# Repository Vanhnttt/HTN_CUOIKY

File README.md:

# DỰ ÁN MÁY HIỆN SÓNG MINI (STM32F103C8T6 + TFT ST7735 1.8")
---
## 📂 CẤU TRÚC DỰ ÁN ĐÃ TÁCH MODULE HOÀN CHỈNH
```text
oscilloscope/
├── .vscode/
│   └── c_cpp_properties.json   (Cấu hình Include & IntelliSense cho VS Code)
├── Core/
│   ├── Inc/
│   │   │   /* --- 1. KHỐI TÍNH TOÁN & XỬ LÝ TÍN HIỆU (THEO ĐỀ BÀI) --- */
│   │   ├── signal_calc.h       (Tìm trigger, tính Vmin/Vmax/Vpp, tần số cắt ngưỡng)
│   │   │
│   │   │   /* --- 2. CÁC MODULE ỨNG DỤNG MÁY HIỆN SÓNG --- */
│   │   ├── scope_acquisition.h (Thu thập ADC1 kích TIM3 TRGO + DMA Double buffer)
│   │   ├── test_signal.h       (Phát xung vuông PWM 1 kHz test sóng tại PA8)
│   │   ├── st7735.h            (Driver màn hình màu TFT ST7735 qua SPI1)
│   │   ├── scope_gui.h         (Hiển thị lưới chia ô, dạng sóng, OSD thông số)
│   │   ├── scope_input.h       (Đọc Rotary Encoder TIM4 & nút bấm PB8, PB9)
│   │   ├── scope_fft.h         (Chế độ FFT hiển thị phổ tần số Radix-2)
│   │   │
│   │   │   /* --- 3. CÁC MODULE NGOẠI VI PHẦN CỨNG (TÁCH KHỎI MAIN) --- */
│   │   ├── sys_clock.h         (Cấu hình xung nhịp 72 MHz: HSE + PLL)
│   │   ├── gpio.h              (Cấu hình chân I/O màn hình, nút bấm, ADC)
│   │   ├── dma.h               (Cấu hình DMA1 Channel 1 cho ADC1)
│   │   ├── adc.h               (Cấu hình ADC1 kích hoạt bởi TIM3 TRGO)
│   │   ├── spi.h               (Cấu hình SPI1 Master 9 MHz)
│   │   ├── tim.h               (Cấu hình TIM1 PWM, TIM3 ADC TRGO, TIM4 Encoder)
│   │   ├── stm32f1xx_it.h      (Khai báo các ngắt hệ thống & ngoại vi)
│   │   └── main.h              (Khai báo thư viện HAL & Error_Handler)
│   │
│   └── Src/
│       ├── main.c              (Hàm main điều phối luồng chạy - RẤT NGẮN GỌN)
│       ├── signal_calc.c       (Thuật toán tính toán Vpp, Freq, Trigger)
│       ├── scope_acquisition.c
│       ├── test_signal.c
│       ├── st7735.c
│       ├── scope_gui.c
│       ├── scope_input.c
│       ├── scope_fft.c
│       ├── sys_clock.c
│       ├── gpio.c
│       ├── dma.c
│       ├── adc.c
│       ├── spi.c
│       ├── tim.c
│       ├── stm32f1xx_it.c      (Hàm phục vụ ngắt DMA, ngắt hệ thống)
│       └── stm32f1xx_hal_msp.c (Hàm MSP cấu hình chân & xung ngoại vi)
└── README.md
```

---

## 📌 CHI TIẾT CÁC HÀM TRONG KHỐI TÍNH TOÁN (`signal_calc.c`)

Khối này giải quyết trọn vẹn yêu cầu trong ảnh:
> *"Xử lý: tìm điểm trigger, tính Vmin/Vmax/Vpp, tần số (đếm cắt ngưỡng)"*

1. **`SigCalc_Tinh_Vmin_Vmax_Vpp(snap_buf)`**:
   - Quét 256 mẫu ADC để tìm mẫu cực tiểu và cực đại.
   - Tính toán điện áp chuẩn: $V_{\min}$, $V_{\max}$ và điện áp đỉnh - đỉnh $V_{\text{pp}} = V_{\max} - V_{\min}$.
2. **`SigCalc_TinhTanSo_DemCatNguong(snap_buf, snap_tb)`**:
   - Xác định ngưỡng trung bình `mid = (max + min)/2` và dải trễ `hyst`.
   - Đếm số lần tín hiệu cắt qua ngưỡng cạnh lên để tính chính xác chu kỳ và tần số tín hiệu $f = \frac{f_s \times (edges - 1)}{\Delta samples}$.
3. **`SigCalc_TimDiemTrigger(snap_buf, trig_lvl)`**:
   - Dò tìm điểm tín hiệu vượt ngưỡng `trig_lvl` theo cạnh lên có dải trễ chống nhiễu (hysteresis) để khóa dạng sóng đứng yên trên màn hình.
4. **`SigCalc_ChuanBiDangSong(...)`**:
   - Ánh xạ các điểm mẫu quanh điểm trigger sang tọa độ cột $X$ và hàng $Y$ trên màn hình ST7735.

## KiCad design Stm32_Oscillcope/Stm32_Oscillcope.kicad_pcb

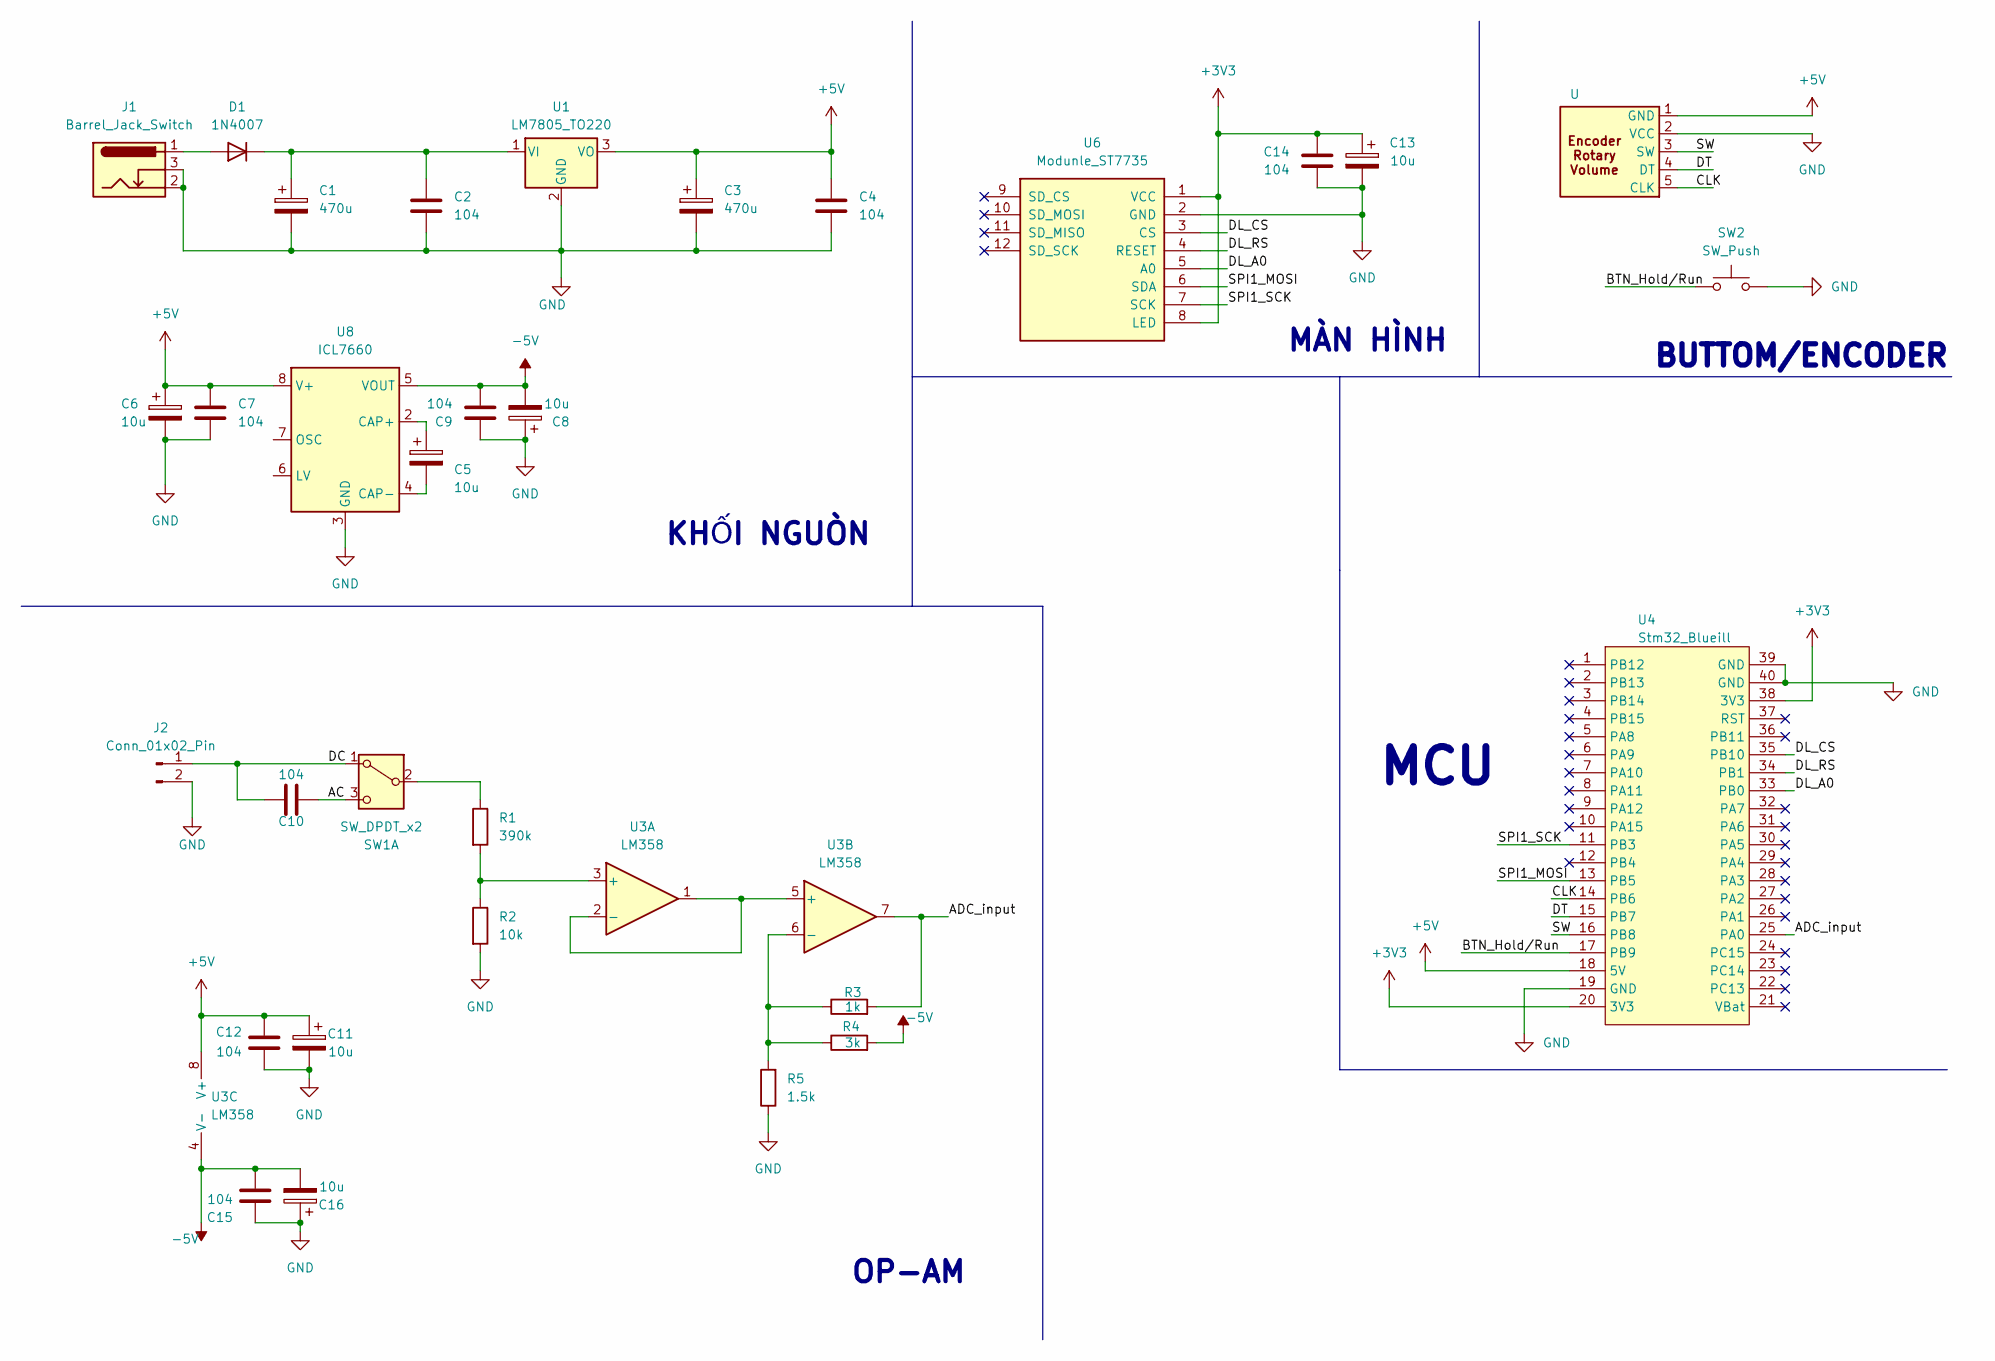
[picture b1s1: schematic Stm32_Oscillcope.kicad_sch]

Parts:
C1, C3: 470u; CP_Radial_D10.0mm_P5.00mm
C2, C4, C7, C9, C10, C12, C14, C15: 104; C_Disc_D3.0mm_W1.6mm_P2.50mm
C5, C6, C11, C13, C16: 10u; CP_Radial_D5.0mm_P2.00mm
C8: 10u; CP_Radial_D5.0mm_P2.50mm
D1: 1N4007; D_DO-41_SOD81_P10.16mm_Horizontal
J1: Barrel_Jack_Switch; BarrelJack_GCT_DCJ200-10-A_Horizontal
J2: Conn_01x02_Pin; TerminalBlock_Phoenix_MKDS-1,5-2_1x02_P5.00mm_Horizontal
R1: 390k; R_Axial_DIN0411_L9.9mm_D3.6mm_P12.70mm_Horizontal
R2: 10k; R_Axial_DIN0411_L9.9mm_D3.6mm_P12.70mm_Horizontal
R3: 1k; R_Axial_DIN0411_L9.9mm_D3.6mm_P12.70mm_Horizontal
R4: 3k; R_Axial_DIN0411_L9.9mm_D3.6mm_P12.70mm_Horizontal
R5: 1.5k; R_Axial_DIN0411_L9.9mm_D3.6mm_P12.70mm_Horizontal
SW1: SW_DPDT_x2; SW_Slide_SPDT_Straight_CK_OS102011MS2Q
SW2: SW_Push; SW_PUSH_6mm
U1: LM7805_TO220; TO-220-3_Vertical
U2: U; Module_Encoder
U3: LM358; DIP-8_W7.62mm_Socket
U4: Stm32_Blueill; YAAJ_BluePill_1
U6: Modunle_ST7735; Display_ST7735
U8: ICL7660; DIP-8_W7.62mm_Socket

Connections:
+3V3: C13.1, C14.1, U4.20 (3V3), U4.38 (3V3), U6.1 (VCC), U6.8 (LED)
+5V: C3.1, C4.1, C6.1, C7.1, C11.1, C12.1, U1.3 (VO), U2.1 (GND), U3.8 (V+), U4.18 (5V), U8.8 (V+)
-5V: C8.2, C9.2, C15.2, C16.2, R4.2, U3.4 (V-), U8.5 (VOUT)
/AC: C10.2, SW1.3 (C)
/ADC_input: R3.2, U3.7, U4.25 (PA0)
/BTN_Hold/Run: SW2.1, U4.17 (PB9)
/CLK: U2.5 (CLK), U4.14 (PB6)
/DC: C10.1, J2.1, SW1.1 (A)
/DL_A0: U4.33 (PB0), U6.5 (A0)
/DL_CS: U4.35 (PB10), U6.3 (CS)
/DL_RS: U4.34 (PB1), U6.4 (RESET)
/DT: U2.4 (DT), U4.15 (PB7)
/SPI1_MOSI: U4.13 (PB5), U6.6 (SDA)
/SPI1_SCK: U4.11 (PB3), U6.7 (SCK)
/SW: U2.3 (SW), U4.16 (PB8)
GND: C1.2, C2.2, C3.2, C4.2, C6.2, C7.2, C8.1, C9.1, C11.2, C12.2, C13.2, C14.2, C15.1, C16.1, J1.2, J1.3, J2.2, R2.2, R5.1, SW2.2, U1.2 (GND), U2.2 (VCC), U4.19 (GND), U4.39 (GND), U4.40 (GND), U6.2 (GND), U8.3 (GND)
unnamed: D1.2 (A), J1.1
unnamed: C1.1, C2.1, D1.1 (K), U1.1 (VI)
unnamed: R1.1, SW1.2 (B)
unnamed: R1.2, R2.1, U3.3 (+)
unnamed: U3.1, U3.2 (-), U3.5 (+)
unnamed: R3.1, R4.1, R5.2, U3.6 (-)
unnamed: C5.1, U8.2 (CAP+)
unnamed: C5.2, U8.4 (CAP-)

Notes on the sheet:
MCU
MÀN HÌNH
KHỐI NGUÒN
BUTTOM/ENCODER
OP-AM

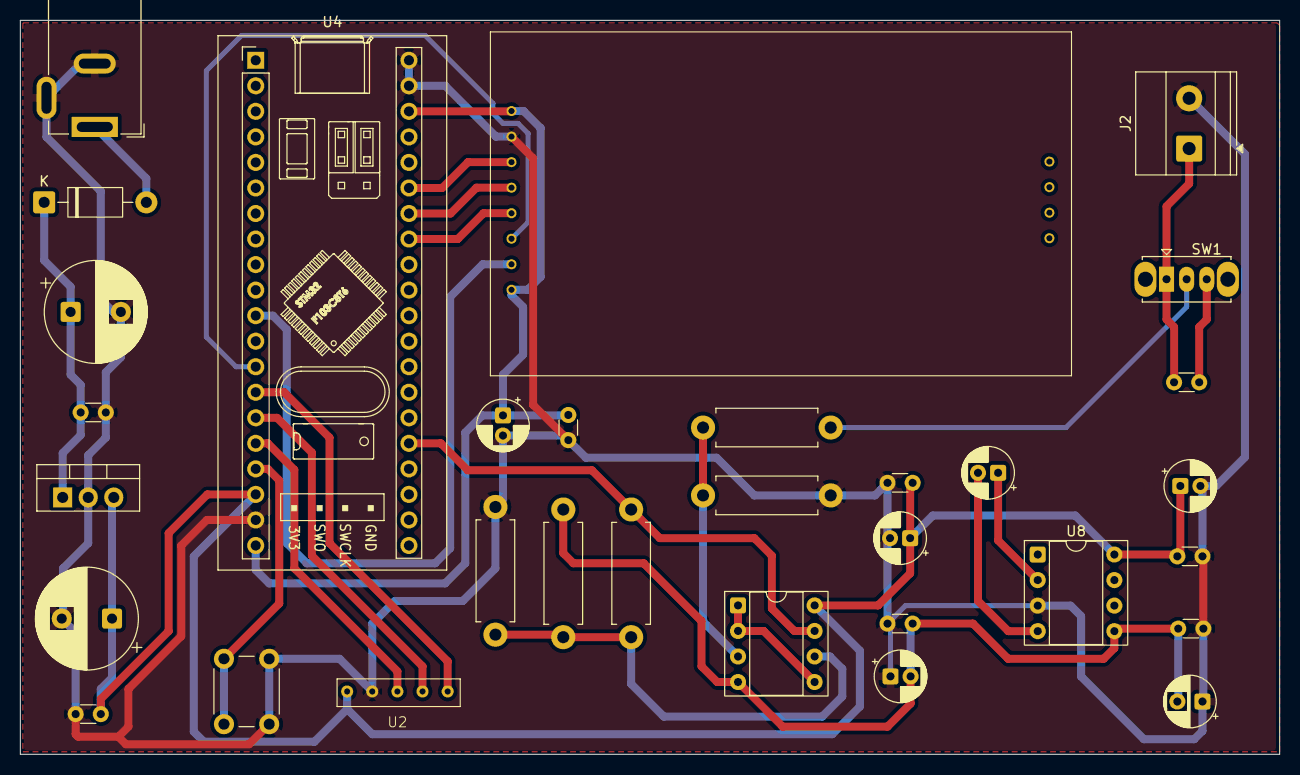
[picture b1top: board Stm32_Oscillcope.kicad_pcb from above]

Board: 2 copper layers, 125.2 x 73.0 mm, 32 parts (0 on the bottom side), 24 nets.

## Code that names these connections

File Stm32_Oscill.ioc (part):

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Mcu.Name=STM32F103C(8-B)Tx
Mcu.Package=LQFP48
Mcu.UserName=STM32F103C8Tx
PA0-WKUP.Signal=ADCx_IN0
PA13.Mode=Serial_Wire
PA13.Signal=SYS_JTMS-SWDIO
PA14.Mode=Serial_Wire
PA14.Signal=SYS_JTCK-SWCLK
PA8.Signal=S_TIM1_CH1
PB0.GPIOParameters=GPIO_Speed,GPIO_Label
PB0.GPIO_Label=DL_A0
PB0.GPIO_Speed=GPIO_SPEED_FREQ_HIGH
PB0.Signal=GPIO_Output
PB1.GPIOParameters=GPIO_Speed,GPIO_Label
PB1.GPIO_Label=DL_RS
PB1.GPIO_Speed=GPIO_SPEED_FREQ_HIGH
PB1.Signal=GPIO_Output
PB10.GPIOParameters=GPIO_Speed,GPIO_Label
PB10.GPIO_Label=DL_CS
PB10.GPIO_Speed=GPIO_SPEED_FREQ_HIGH
PB10.Signal=GPIO_Output
PB3.Mode=TX_Only_Simplex_Unidirect_Master
PB3.Signal=SPI1_SCK
PB5.Mode=TX_Only_Simplex_Unidirect_Master
PB5.Signal=SPI1_MOSI
PB6.Signal=S_TIM4_CH1
PB7.Signal=S_TIM4_CH2
PB8.GPIOParameters=GPIO_PuPd,GPIO_Label
PB8.GPIO_Label=SW
PB8.GPIO_PuPd=GPIO_PULLUP
PB8.Signal=GPIO_Input
PB9.GPIOParameters=GPIO_Label
PB9.GPIO_Label=BTN_RUN/HOLD
PB9.Signal=GPIO_Input
PD0-OSC_IN.Mode=HSE-External-Oscillator
PD0-OSC_IN.Signal=RCC_OSC_IN
PD1-OSC_OUT.Mode=HSE-External-Oscillator
PD1-OSC_OUT.Signal=RCC_OSC_OUT
RCC.SYSCLKFreq_VALUE=72000000
RCC.SYSCLKSource=RCC_SYSCLKSOURCE_PLLCLK
board=custom
